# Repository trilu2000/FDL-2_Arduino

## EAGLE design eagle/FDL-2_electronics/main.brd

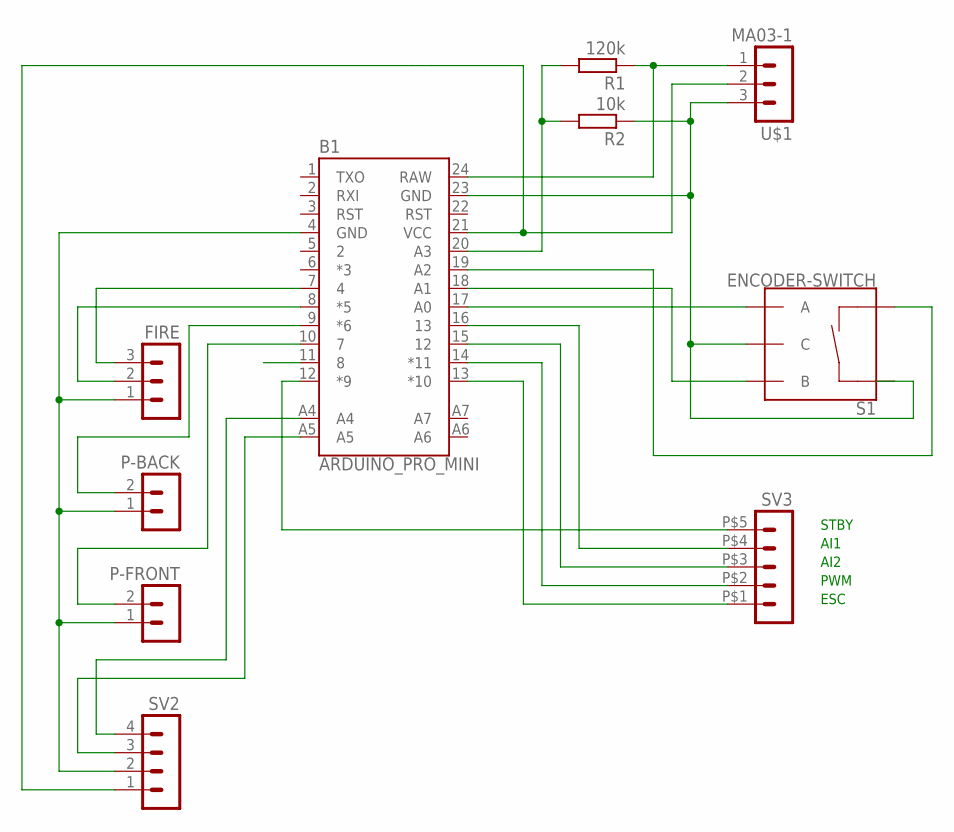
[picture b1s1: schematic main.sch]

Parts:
B1: ARDUINO_PRO_MINI; ARDUINO_PRO_MINI_WO
FIRE: MA03-1
P-BACK: MA02-1
P-FRONT: MA02-1
R1: 120k; 0204/5
R2: 10k; 0204V
S1: ENCODER-SWITCH; ROTARY_ENC_PLAIN
SV2: MA04-1
SV3: MA05-1
U$1: MA03-1

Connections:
unnamed: B1.24 (RAW), R1.1, U$1.1
unnamed: B1.12 (*9), SV3.P$5 (5)
unnamed: B1.7 (4), FIRE.3
unnamed: B1.4 (GND), FIRE.1, P-BACK.1 (2), P-FRONT.1 (2), SV2.2
unnamed: B1.8 (*5), FIRE.2
unnamed: B1.18 (A1), S1.B
unnamed: B1.9 (*6), P-BACK.2 (3)
unnamed: B1.10 (7), P-FRONT.2 (3)
unnamed: B1.17 (A0), S1.A
unnamed: B1.19 (A2), S1.SW-
unnamed: B1.23 (GND), R2.1, S1.C, U$1.3
unnamed: B1.20 (A3), R1.2, R2.2
unnamed: B1.A4, SV2.4
unnamed: B1.A5, SV2.3
unnamed: B1.16 (13), SV3.P$4 (4)
unnamed: B1.15 (12), SV3.P$3 (3)
unnamed: B1.14 (*11), SV3.P$2 (2)
unnamed: B1.13 (*10), SV3.P$1 (1)
unnamed: B1.21 (VCC), SV2.1, U$1.2

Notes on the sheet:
ESC
PWM
AI2
AI1
STBY

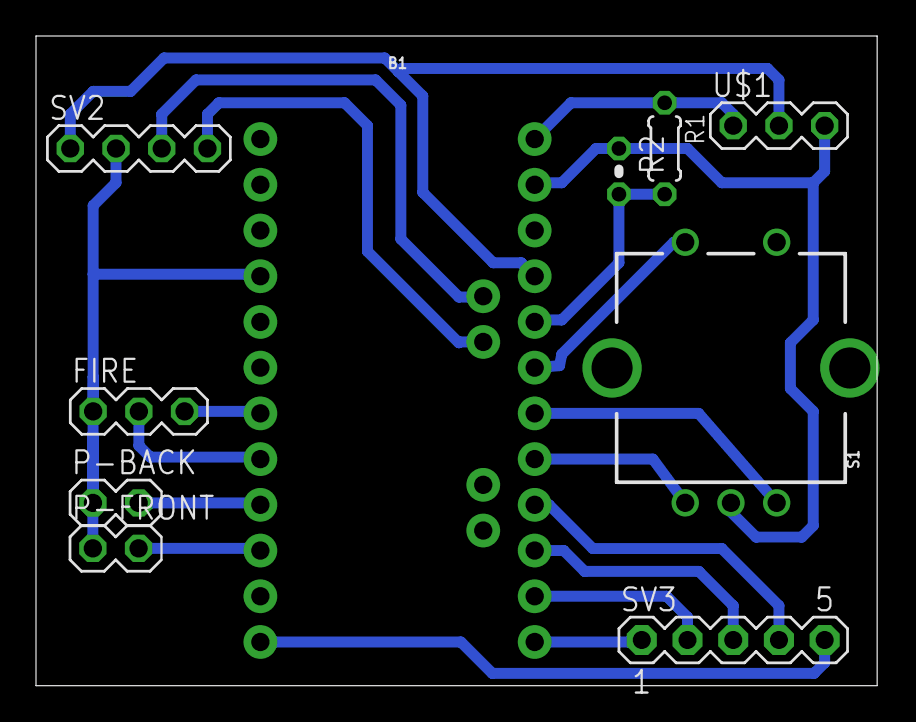
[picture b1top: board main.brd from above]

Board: 2 copper layers, 46.7 x 36.1 mm, 10 parts (0 on the bottom side), 19 nets.

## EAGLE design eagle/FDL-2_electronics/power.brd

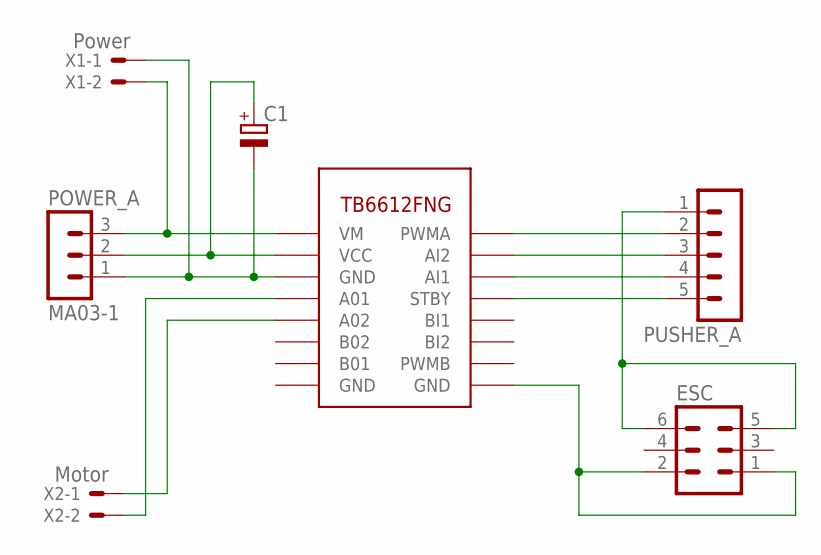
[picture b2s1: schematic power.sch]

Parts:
C1: CPOL-EUTT5D7; TT5D7
ESC: MA03-2
POWER_A: MA03-1
PUSHER_A: MA05-1
U$2: TB6612FNG
X1: Power; JST-XH-02-PACKAGE-ROUND-PAD
X2: Motor; JST-XH-02-PACKAGE-ROUND-PAD

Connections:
unnamed: U$2.P$4 (A01), X2.2
unnamed: U$2.P$5 (A02), X2.1
unnamed: PUSHER_A.4, U$2.P$14 (AI1)
unnamed: POWER_A.3, U$2.P$1 (VM), X1.2
unnamed: C1.-, POWER_A.1, U$2.P$3 (GND), X1.1
unnamed: PUSHER_A.5, U$2.P$13 (STBY)
unnamed: PUSHER_A.3, U$2.P$15 (AI2)
unnamed: PUSHER_A.2, U$2.P$16 (PWMA)
unnamed: ESC.1, ESC.2, U$2.P$9 (GND)
unnamed: ESC.5, ESC.6, PUSHER_A.1
unnamed: C1.+, POWER_A.2, U$2.P$2 (VCC)

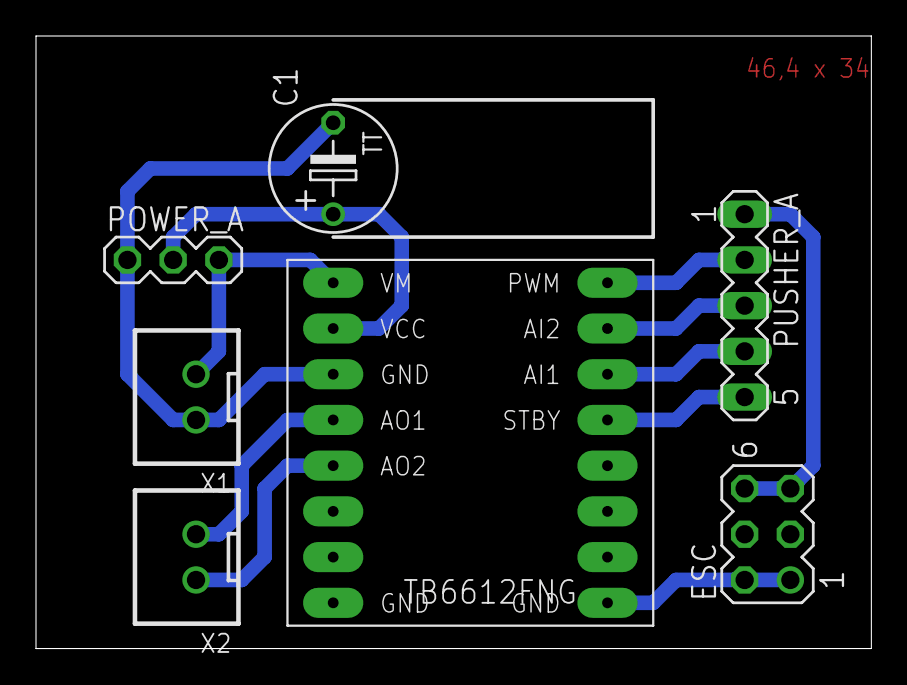
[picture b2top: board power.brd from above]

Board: 2 copper layers, 46.4 x 34.0 mm, 7 parts (0 on the bottom side), 11 nets.

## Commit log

2017-12-18 :boom::camel: Added .gitattributes & .gitignore files
2017-12-18 Create test
2017-12-18 new commit
2017-12-21 some fixes
2017-12-23 some changes
2017-12-29 some further changes
2017-12-29 new gitignore
2017-12-29 test
2017-12-29 some update
2018-01-01 some updates - pure functionality is implemented, menu missing
2018-01-15 some further work - mainly on pusher
2018-01-17 pusher via pc interrupt, cleanup of code - working now!!!!!!!!
2018-01-24 save settings in eeprom implemented
2018-04-29 pdf version
2018-05-11 update resistors

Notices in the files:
parts and their libraries:
SparkFun-Boards: Licensing: Creative Commons ShareAlike 4.0 International - https://creativecommons.org/licenses/by-sa/4.0
